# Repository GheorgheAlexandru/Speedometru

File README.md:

# Proiect KiCad Cluster Contor de Viteza

## Prezentare Generală
Acest proiect implică proiectarea unui cluster de contor de viteza folosind KiCad, un software gratuit pentru proiectarea electronica . Clusterul de contor de viteza va afisa citirile vitezei si alte date relevante pentru aplicatiile automotive.

## Caracteristici
- Afisaj digital pentru citirile vitezei
- Ecrane analogice optionale pentru RPM si nivelul carburantului
- Intrari pentru senzori de viteza si alte periferice
- Aspect PCB personalizabil

## Introducere
### Cerinte
- Instalare KiCad (versiunea 6.0 sau mai noua se recomanda)
- Cunostinte de baza ale electronicii si proiectarii PCB

### Instalare
1. Cloneaza acest depozit:
    ```bash
    git clone https://github.com/GheorgheAlexandru/Speedometru.git
    ```
2. Deschide fisierul proiectului KiCad (`.kicad_sch`) in KiCad.
4. Verifica schema si aspectul, efectueaza orice ajustari necesare in functie de nevoile tale.

## Contributii
Contributiile sunt binevenite! Te rog creeaza o cerere de tragere (pull request) sau trimite probleme pentru imbunatatiri sau bug-uri.

## Licenta
Acest proiect este autorizat sub Licenta MIT. Vezi fisierul LICENSE pentru mai multe detalii.

## Contact
Pentru orice intrebari sau sugestii, simte-te liber sa ma contactezi pe GitHub: [GheorgheAlexandru](https://github.com/GheorgheAlexandru)

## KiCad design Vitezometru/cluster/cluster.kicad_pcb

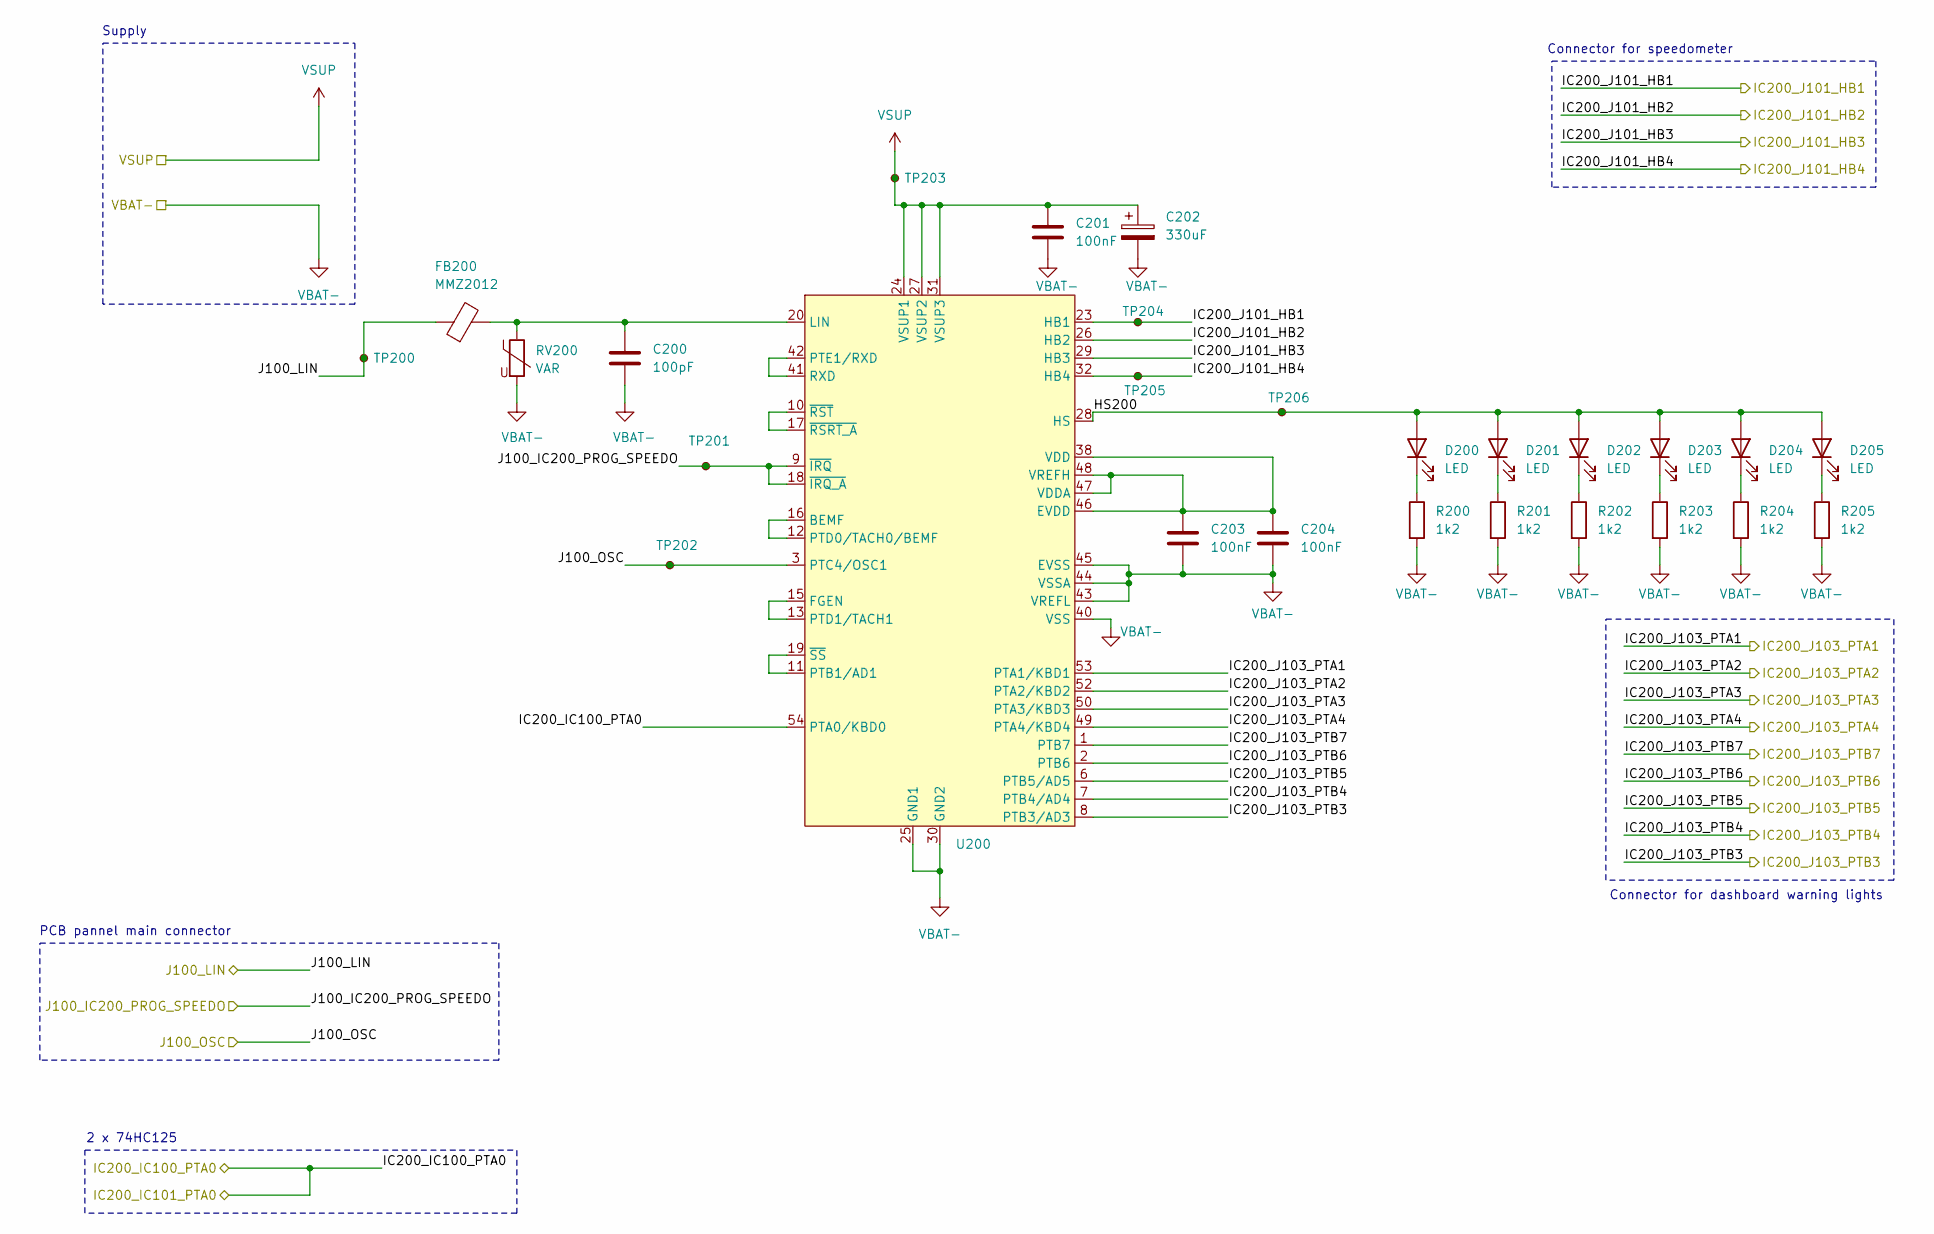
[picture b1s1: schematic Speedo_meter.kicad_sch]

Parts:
C200: 100pF; C_0402_1005Metric_Pad0.74x0.62mm_HandSolder
C201, C203, C204: 100nF; C_0402_1005Metric_Pad0.74x0.62mm_HandSolder
C202: 330uF; CP_EIA-7343-15_Kemet-W
D200, D201, D202, D203, D204, D205: LED; LED_1206_3216Metric
FB200: MMZ2012; L_0805_2012Metric
R200, R201, R202, R203, R204, R205: 1k2; R_0402_1005Metric_Pad0.72x0.64mm_HandSolder
RV200: VAR; R_0603_1608Metric_Pad0.98x0.95mm_HandSolder
TP200, TP201, TP202, TP203, TP204, TP205, TP206: TestPoint_Small; TestPoint_Pad_D1.0mm
U200: SOP65P1030X245-55N; Manufacturer_Part_Number MM908E625ACEK; Mouser Part Number 841-MM908E625ACEK

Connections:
/Speedo_meter/HS200: D200.2 (A), D201.2 (A), D202.2 (A), D203.2 (A), D204.2 (A), D205.2 (A), TP206.1, U200.28 (HS)
/Speedo_meter/IC200_IC100_PTA0: U200.54 (PTA0/KBD0); also elsewhere on the board
/Speedo_meter/IC200_J101_HB1: TP204.1, U200.23 (HB1); also elsewhere on the board
/Speedo_meter/IC200_J101_HB2: U200.26 (HB2); also elsewhere on the board
/Speedo_meter/IC200_J101_HB3: U200.29 (HB3); also elsewhere on the board
/Speedo_meter/IC200_J101_HB4: TP205.1, U200.32 (HB4); also elsewhere on the board
/Speedo_meter/IC200_J103_PTA1: U200.53 (PTA1/KBD1); also elsewhere on the board
/Speedo_meter/IC200_J103_PTA2: U200.52 (PTA2/KBD2); also elsewhere on the board
/Speedo_meter/IC200_J103_PTA3: U200.50 (PTA3/KBD3); also elsewhere on the board
/Speedo_meter/IC200_J103_PTA4: U200.49 (PTA4/KBD4); also elsewhere on the board
/Speedo_meter/IC200_J103_PTB3: U200.8 (PTB3/AD3); also elsewhere on the board
/Speedo_meter/IC200_J103_PTB4: U200.7 (PTB4/AD4); also elsewhere on the board
/Speedo_meter/IC200_J103_PTB5: U200.6 (PTB5/AD5); also elsewhere on the board
/Speedo_meter/IC200_J103_PTB6: U200.2 (PTB6); also elsewhere on the board
/Speedo_meter/IC200_J103_PTB7: U200.1 (PTB7); also elsewhere on the board
/Speedo_meter/J100_IC200_PROG_SPEEDO: TP201.1, U200.9 (~IRQ), U200.18 (~IRQ_A); also elsewhere on the board
/Speedo_meter/J100_LIN: FB200.1, TP200.1; also elsewhere on the board
/Speedo_meter/J100_OSC: TP202.1, U200.3 (PTC4/OSC1); also elsewhere on the board
unnamed: D200.1 (K), R200.1
unnamed: D201.1 (K), R201.1
unnamed: D202.1 (K), R202.1
unnamed: D203.1 (K), R203.1
unnamed: D204.1 (K), R204.1
unnamed: D205.1 (K), R205.1
unnamed: U200.12 (PTD0/TACH0/BEMF), U200.16 (BEMF)
unnamed: C203.1, C204.1, U200.38 (VDD), U200.46 (EVDD), U200.47 (VDDA), U200.48 (VREFH)
unnamed: U200.13 (PTD1/TACH1), U200.15 (FGEN)
unnamed: C200.1, FB200.2, RV200.1, U200.20 (LIN)
unnamed: U200.11 (PTB1/AD1), U200.19 (~SS)
unnamed: U200.41 (RXD), U200.42 (PTE1/RXD)
unnamed: U200.10 (~RST), U200.17 (~RSRT_A)
VBAT-: C200.2, C201.2, C202.2, C203.2, C204.2, R200.2, R201.2, R202.2, R203.2, R204.2, R205.2, RV200.2, U200.25 (GND1), U200.30 (GND2), U200.40 (VSS), U200.43 (VREFL), U200.44 (VSSA), U200.45 (EVSS); also elsewhere on the board
VSUP: C201.1, C202.1, TP203.1, U200.24 (VSUP1), U200.27 (VSUP2), U200.31 (VSUP3); also elsewhere on the board

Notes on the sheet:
2 x 74HC125
Connector for speedometer
PCB pannel main connector
Supply
Connector for dashboard warning lights

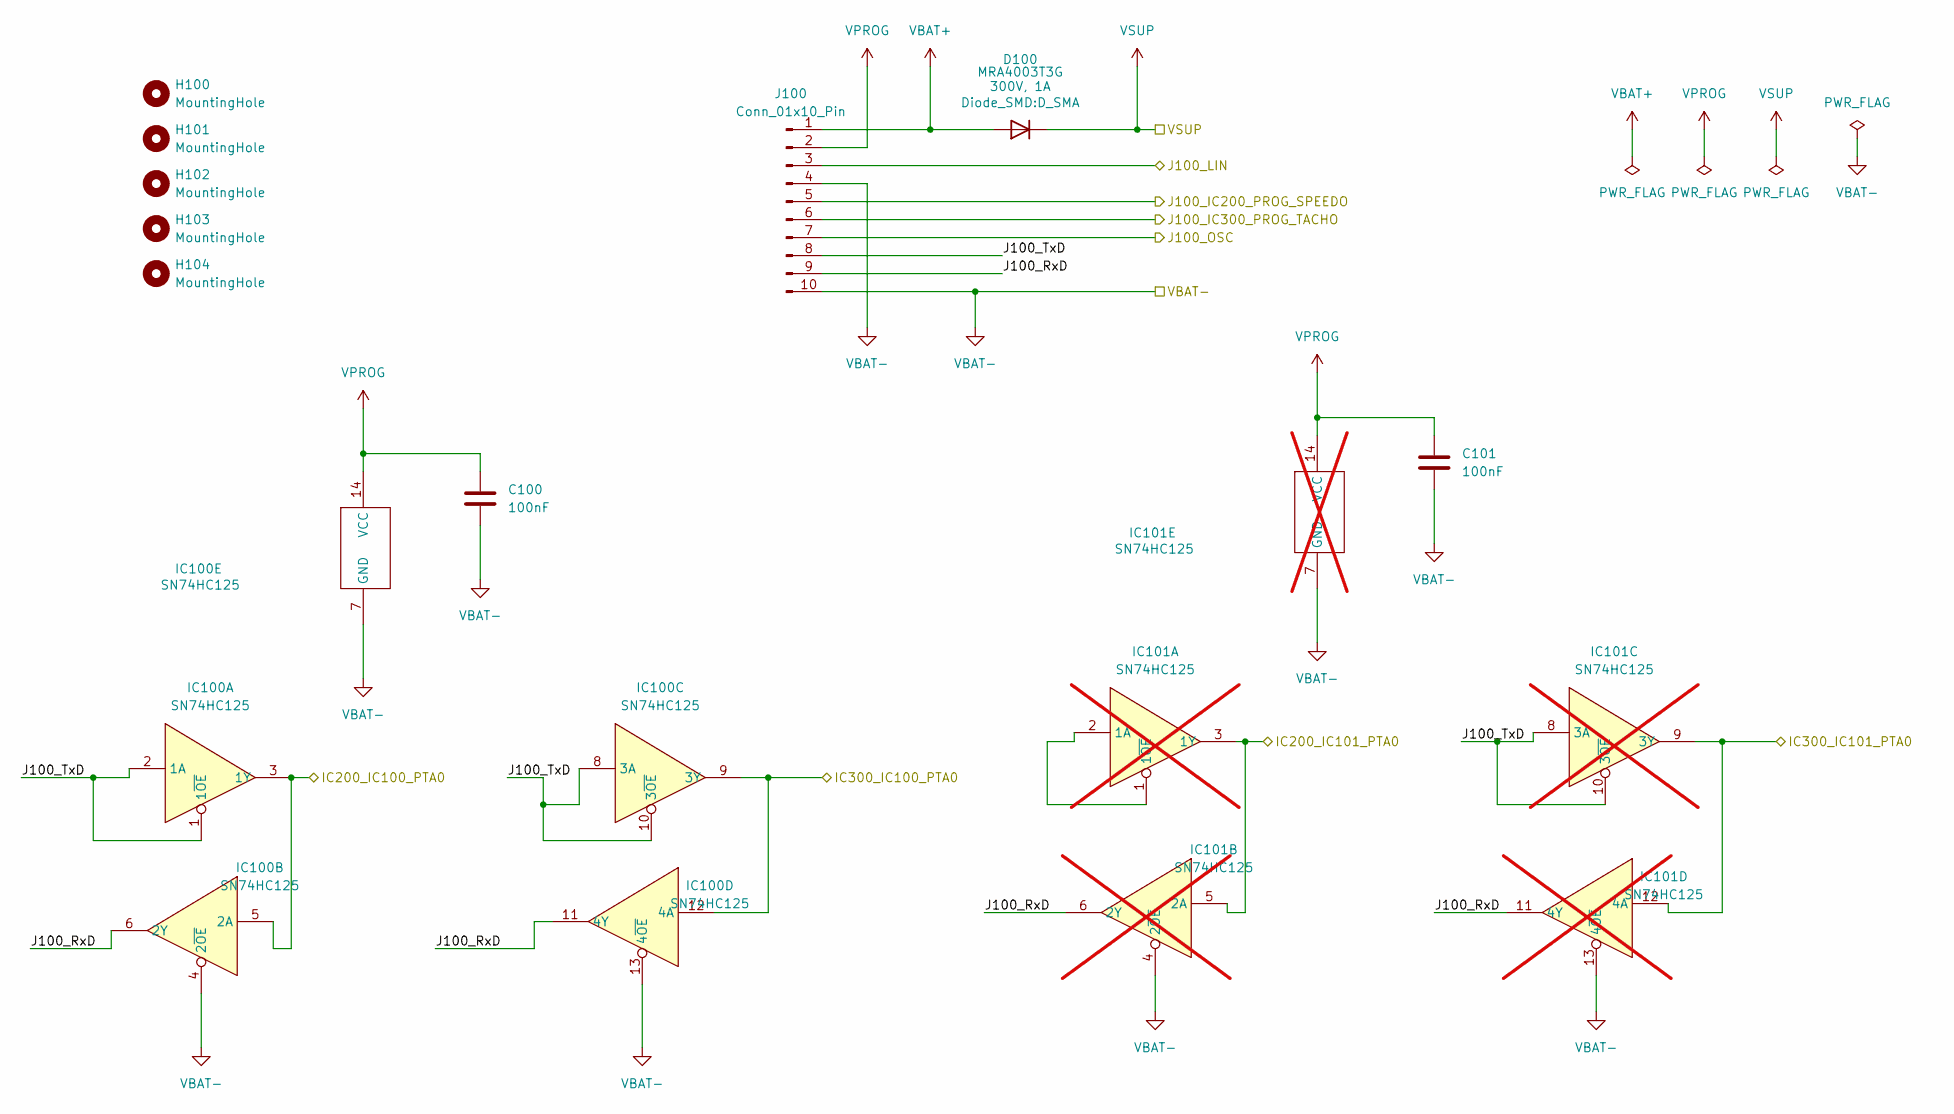
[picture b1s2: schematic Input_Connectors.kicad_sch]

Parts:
C100, C101: 100nF; C_0402_1005Metric_Pad0.74x0.62mm_HandSolder
D100: MRA4003T3G; D_SMA
H100, H101, H102, H103, H104: MountingHole; MountingHole_5mm
IC100: SN74HC125; SOIC-14_3.9x8.7mm_P1.27mm
IC101: SN74HC125; TSSOP-14_4.4x5mm_P0.65mm; not fitted
J100: Conn_01x10_Pin; PinHeader_1x10_P2.54mm_Vertical

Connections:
/Input_Connectors/J100_RxD: IC100.6 (2Y), IC100.11 (4Y), IC101.6 (2Y), IC101.11 (4Y), J100.9
/Input_Connectors/J100_TxD: IC100.1 (1~OE), IC100.2 (1A), IC100.8 (3A), IC100.10 (3~OE), IC101.8 (3A), IC101.10 (3~OE), J100.8
/Speedo_meter/IC200_IC100_PTA0: IC100.3 (1Y), IC100.5 (2A), IC101.3 (1Y), IC101.5 (2A); also elsewhere on the board
/Speedo_meter/J100_IC200_PROG_SPEEDO: J100.5; also elsewhere on the board
/Speedo_meter/J100_LIN: J100.3; also elsewhere on the board
/Speedo_meter/J100_OSC: J100.7; also elsewhere on the board
/Tachometer/IC300_IC100_PTA0: IC100.9 (3Y), IC100.12 (4A), IC101.9 (3Y), IC101.12 (4A); also elsewhere on the board
/Tachometer/J100_IC300_PROG_TACHO: J100.6; also elsewhere on the board
unnamed: IC101.1 (1~OE), IC101.2 (1A)
VBAT+: D100.2 (A), J100.1
VBAT-: C100.2, C101.2, IC100.4 (2~OE), IC100.7 (GND), IC100.13 (4~OE), IC101.4 (2~OE), IC101.7 (GND), IC101.13 (4~OE), J100.4, J100.10; also elsewhere on the board
VPROG: C100.1, C101.1, IC100.14 (VCC), IC101.14 (VCC), J100.2
VSUP: D100.1 (K); also elsewhere on the board

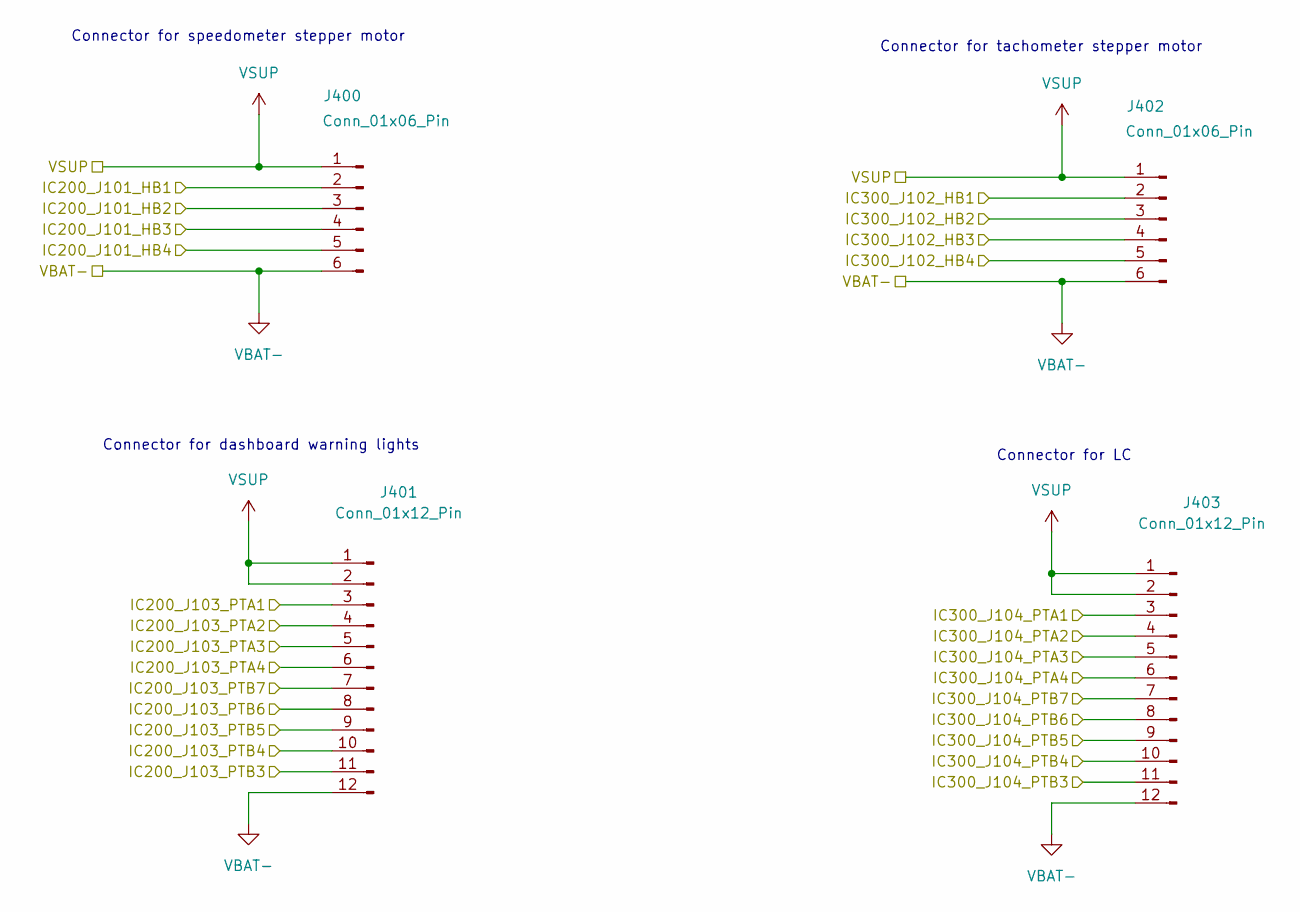
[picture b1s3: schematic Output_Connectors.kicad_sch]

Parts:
J400, J402: Conn_01x06_Pin; PinHeader_1x06_P2.54mm_Vertical
J401, J403: Conn_01x12_Pin; PinHeader_1x12_P2.54mm_Vertical

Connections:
/Speedo_meter/IC200_J101_HB1: J400.2; also elsewhere on the board
/Speedo_meter/IC200_J101_HB2: J400.3; also elsewhere on the board
/Speedo_meter/IC200_J101_HB3: J400.4; also elsewhere on the board
/Speedo_meter/IC200_J101_HB4: J400.5; also elsewhere on the board
/Speedo_meter/IC200_J103_PTA1: J401.3; also elsewhere on the board
/Speedo_meter/IC200_J103_PTA2: J401.4; also elsewhere on the board
/Speedo_meter/IC200_J103_PTA3: J401.5; also elsewhere on the board
/Speedo_meter/IC200_J103_PTA4: J401.6; also elsewhere on the board
/Speedo_meter/IC200_J103_PTB3: J401.11; also elsewhere on the board
/Speedo_meter/IC200_J103_PTB4: J401.10; also elsewhere on the board
/Speedo_meter/IC200_J103_PTB5: J401.9; also elsewhere on the board
/Speedo_meter/IC200_J103_PTB6: J401.8; also elsewhere on the board
/Speedo_meter/IC200_J103_PTB7: J401.7; also elsewhere on the board
/Tachometer/IC300_J102_HB1: J402.2; also elsewhere on the board
/Tachometer/IC300_J102_HB2: J402.3; also elsewhere on the board
/Tachometer/IC300_J102_HB3: J402.4; also elsewhere on the board
/Tachometer/IC300_J102_HB4: J402.5; also elsewhere on the board
/Tachometer/IC300_J104_PTA1: J403.3; also elsewhere on the board
/Tachometer/IC300_J104_PTA2: J403.4; also elsewhere on the board
/Tachometer/IC300_J104_PTA3: J403.5; also elsewhere on the board
/Tachometer/IC300_J104_PTA4: J403.6; also elsewhere on the board
/Tachometer/IC300_J104_PTB3: J403.11; also elsewhere on the board
/Tachometer/IC300_J104_PTB4: J403.10; also elsewhere on the board
/Tachometer/IC300_J104_PTB5: J403.9; also elsewhere on the board
/Tachometer/IC300_J104_PTB6: J403.8; also elsewhere on the board
/Tachometer/IC300_J104_PTB7: J403.7; also elsewhere on the board
VBAT-: J400.6, J401.12, J402.6, J403.12; also elsewhere on the board
VSUP: J400.1, J401.1, J401.2, J402.1, J403.1, J403.2; also elsewhere on the board

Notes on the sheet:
Connector for tachometer stepper motor
Connector for speedometer stepper motor
Connector for LC
Connector for dashboard warning lights

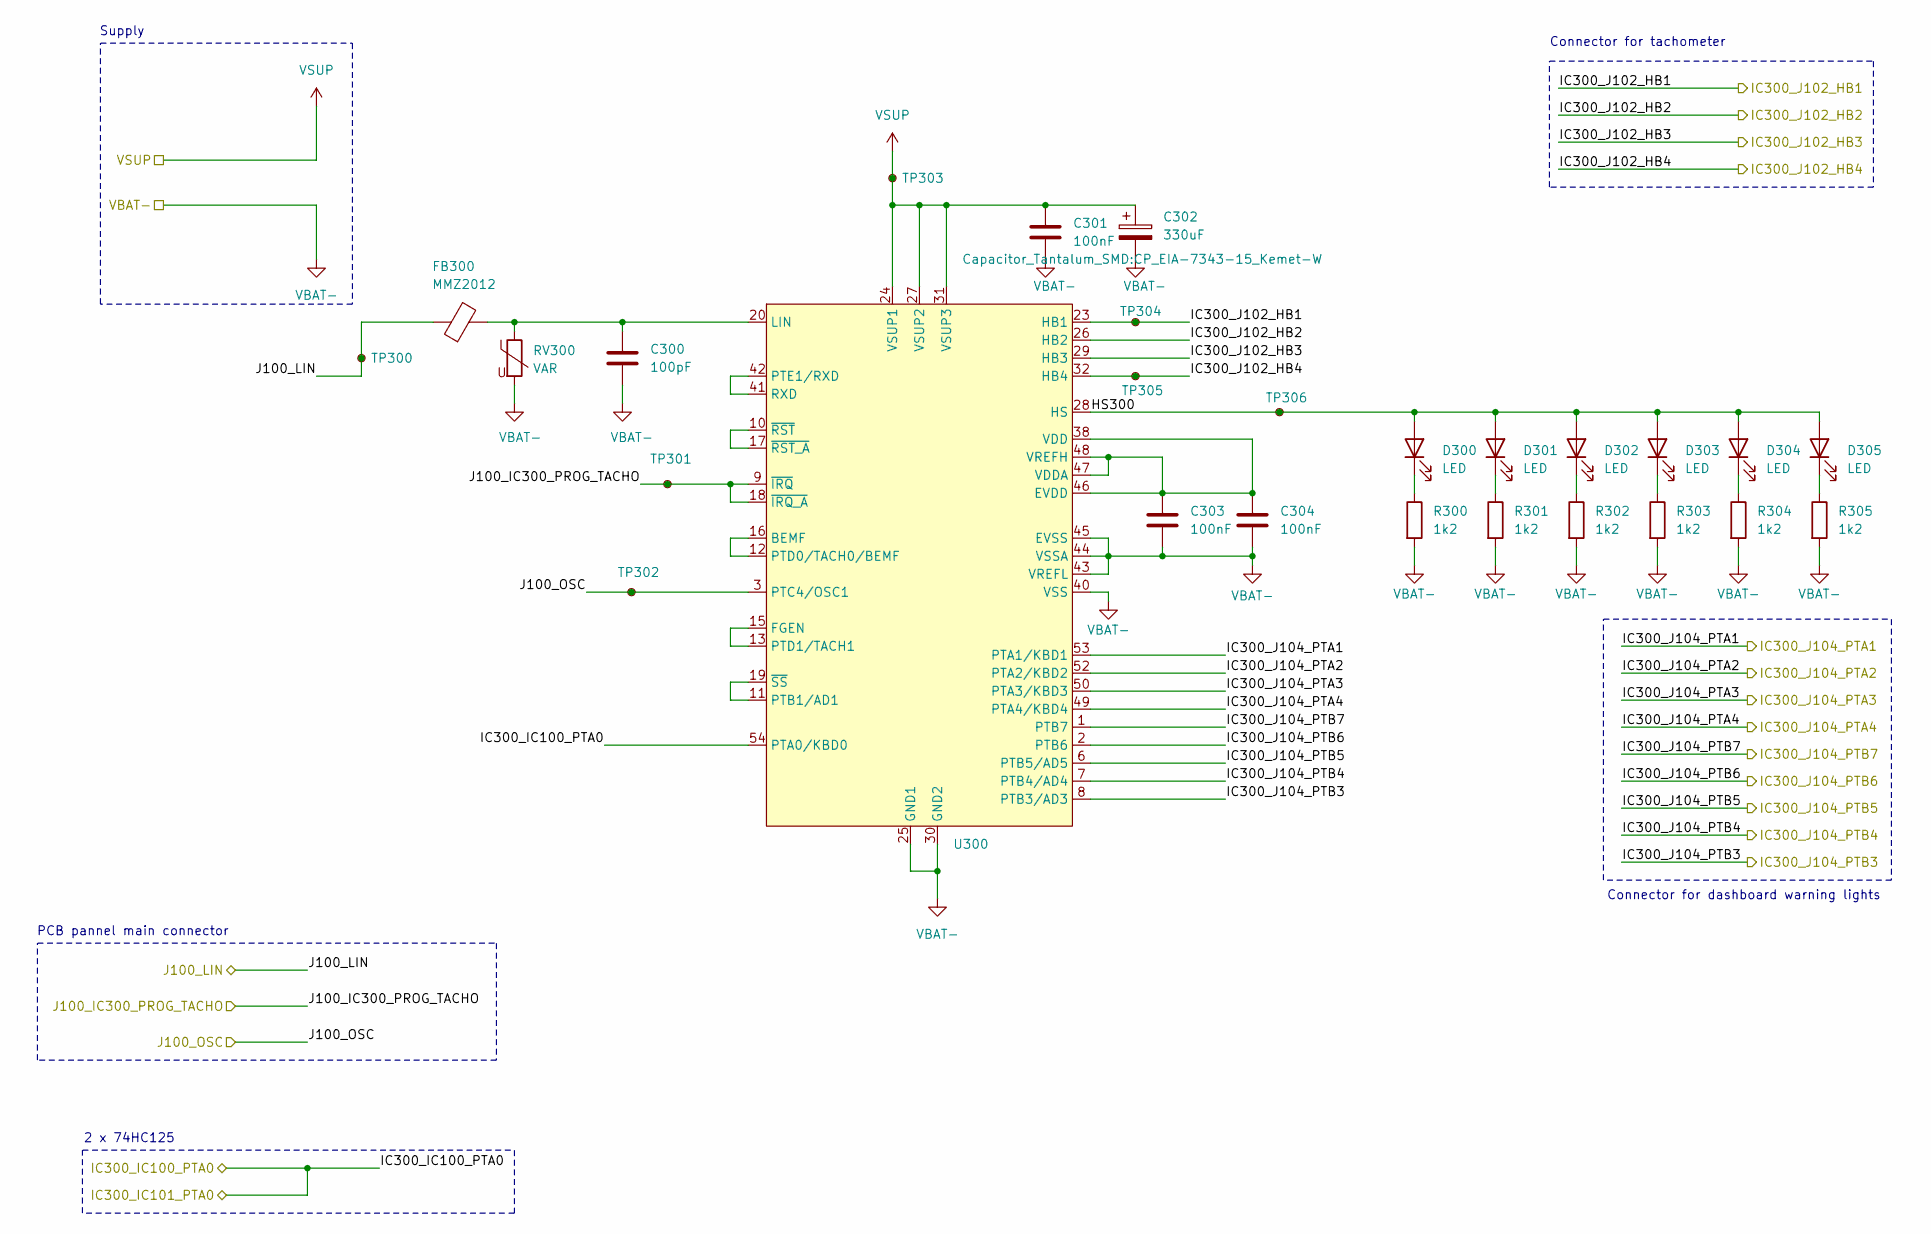
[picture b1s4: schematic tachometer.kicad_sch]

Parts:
C300: 100pF; C_0402_1005Metric_Pad0.74x0.62mm_HandSolder
C301, C303, C304: 100nF; C_0402_1005Metric_Pad0.74x0.62mm_HandSolder
C302: 330uF; CP_EIA-7343-15_Kemet-W
D300, D301, D302, D303, D304, D305: LED; LED_1206_3216Metric
FB300: MMZ2012; L_0805_2012Metric
R300, R301, R302, R303, R304, R305: 1k2; R_0402_1005Metric_Pad0.72x0.64mm_HandSolder
RV300: VAR; R_0603_1608Metric_Pad0.98x0.95mm_HandSolder
TP300, TP301, TP302, TP303, TP304, TP305, TP306: TestPoint_Small; TestPoint_Pad_D1.0mm
U300: SOP65P1030X245-55N

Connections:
/Speedo_meter/J100_LIN: FB300.1, TP300.1; also elsewhere on the board
/Speedo_meter/J100_OSC: TP302.1, U300.3 (PTC4/OSC1); also elsewhere on the board
/Tachometer/HS300: D300.2 (A), D301.2 (A), D302.2 (A), D303.2 (A), D304.2 (A), D305.2 (A), TP306.1, U300.28 (HS)
/Tachometer/IC300_IC100_PTA0: U300.54 (PTA0/KBD0); also elsewhere on the board
/Tachometer/IC300_J102_HB1: TP304.1, U300.23 (HB1); also elsewhere on the board
/Tachometer/IC300_J102_HB2: U300.26 (HB2); also elsewhere on the board
/Tachometer/IC300_J102_HB3: U300.29 (HB3); also elsewhere on the board
/Tachometer/IC300_J102_HB4: TP305.1, U300.32 (HB4); also elsewhere on the board
/Tachometer/IC300_J104_PTA1: U300.53 (PTA1/KBD1); also elsewhere on the board
/Tachometer/IC300_J104_PTA2: U300.52 (PTA2/KBD2); also elsewhere on the board
/Tachometer/IC300_J104_PTA3: U300.50 (PTA3/KBD3); also elsewhere on the board
/Tachometer/IC300_J104_PTA4: U300.49 (PTA4/KBD4); also elsewhere on the board
/Tachometer/IC300_J104_PTB3: U300.8 (PTB3/AD3); also elsewhere on the board
/Tachometer/IC300_J104_PTB4: U300.7 (PTB4/AD4); also elsewhere on the board
/Tachometer/IC300_J104_PTB5: U300.6 (PTB5/AD5); also elsewhere on the board
/Tachometer/IC300_J104_PTB6: U300.2 (PTB6); also elsewhere on the board
/Tachometer/IC300_J104_PTB7: U300.1 (PTB7); also elsewhere on the board
/Tachometer/J100_IC300_PROG_TACHO: TP301.1, U300.9 (~IRQ), U300.18 (~IRQ_A); also elsewhere on the board
unnamed: D300.1 (K), R300.1
unnamed: D301.1 (K), R301.1
unnamed: D302.1 (K), R302.1
unnamed: D303.1 (K), R303.1
unnamed: D304.1 (K), R304.1
unnamed: D305.1 (K), R305.1
unnamed: U300.12 (PTD0/TACH0/BEMF), U300.16 (BEMF)
unnamed: C303.1, C304.1, U300.38 (VDD), U300.46 (EVDD), U300.47 (VDDA), U300.48 (VREFH)
unnamed: U300.13 (PTD1/TACH1), U300.15 (FGEN)
unnamed: C300.1, FB300.2, RV300.1, U300.20 (LIN)
unnamed: U300.11 (PTB1/AD1), U300.19 (~SS)
unnamed: U300.41 (RXD), U300.42 (PTE1/RXD)
unnamed: U300.10 (~RST), U300.17 (~RST_A)
VBAT-: C300.2, C301.2, C302.2, C303.2, C304.2, R300.2, R301.2, R302.2, R303.2, R304.2, R305.2, RV300.2, U300.25 (GND1), U300.30 (GND2), U300.40 (VSS), U300.43 (VREFL), U300.44 (VSSA), U300.45 (EVSS); also elsewhere on the board
VSUP: C301.1, C302.1, TP303.1, U300.24 (VSUP1), U300.27 (VSUP2), U300.31 (VSUP3); also elsewhere on the board

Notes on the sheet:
2 x 74HC125
Connector for dashboard warning lights
Connector for tachometer
PCB pannel main connector
Supply

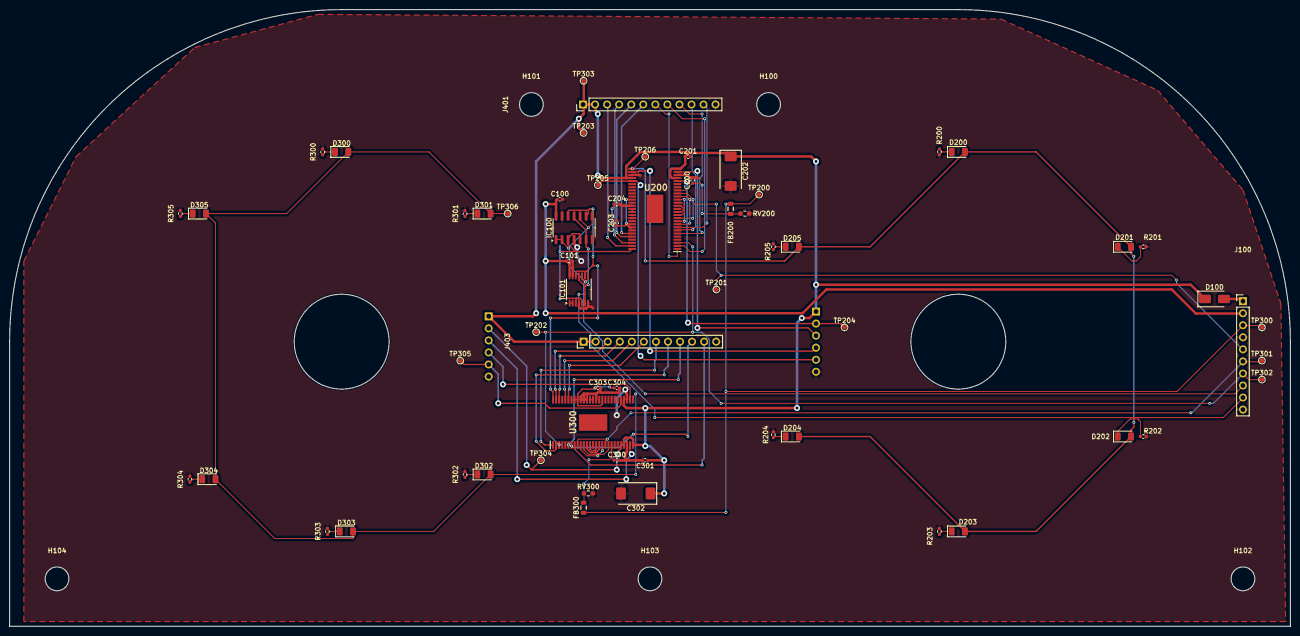
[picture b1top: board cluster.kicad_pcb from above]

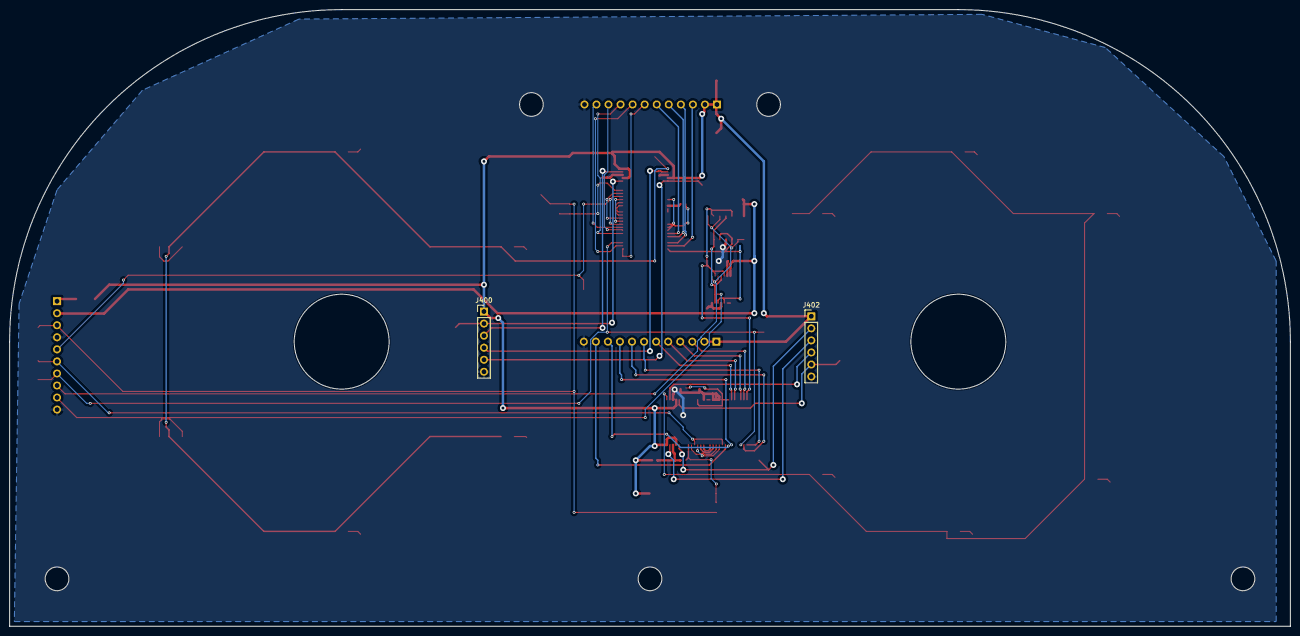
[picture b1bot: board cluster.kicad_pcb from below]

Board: 2 copper layers, 270.0 x 130.0 mm, 69 parts (2 on the bottom side), 67 nets.

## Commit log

2026-03-29 Add professional README for KiCad Speedometer Cluster project
2026-03-29 Update README.md with project details
2026-03-29 Update project description in README.md
    Removed 'EDA' from the description for clarity.
2026-03-30 Update KiCad project file references in README
2026-04-05 Update README.md to add video demonstration section
